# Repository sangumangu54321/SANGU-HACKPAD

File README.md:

SANGU-HACKPAD
Its my personal hackpad made with the help of hack club

# here is the Schematic

# here is the pcb 

# case 

#BOM:
- 6x Cherry MX Switches
- 6x Blank DSA Keycaps
- 3x SK6812 MINI-E LEDs
- 1x XIAO RP2040
- 1x 0.91 inch OLED display
- 4x M3x16 Bolt
- 4x M3 Heatset
- 1x RotaryEncoder_Alps_EC11E_Vertical_H20mm
PLUS 
PCB
FORM JLBPCB

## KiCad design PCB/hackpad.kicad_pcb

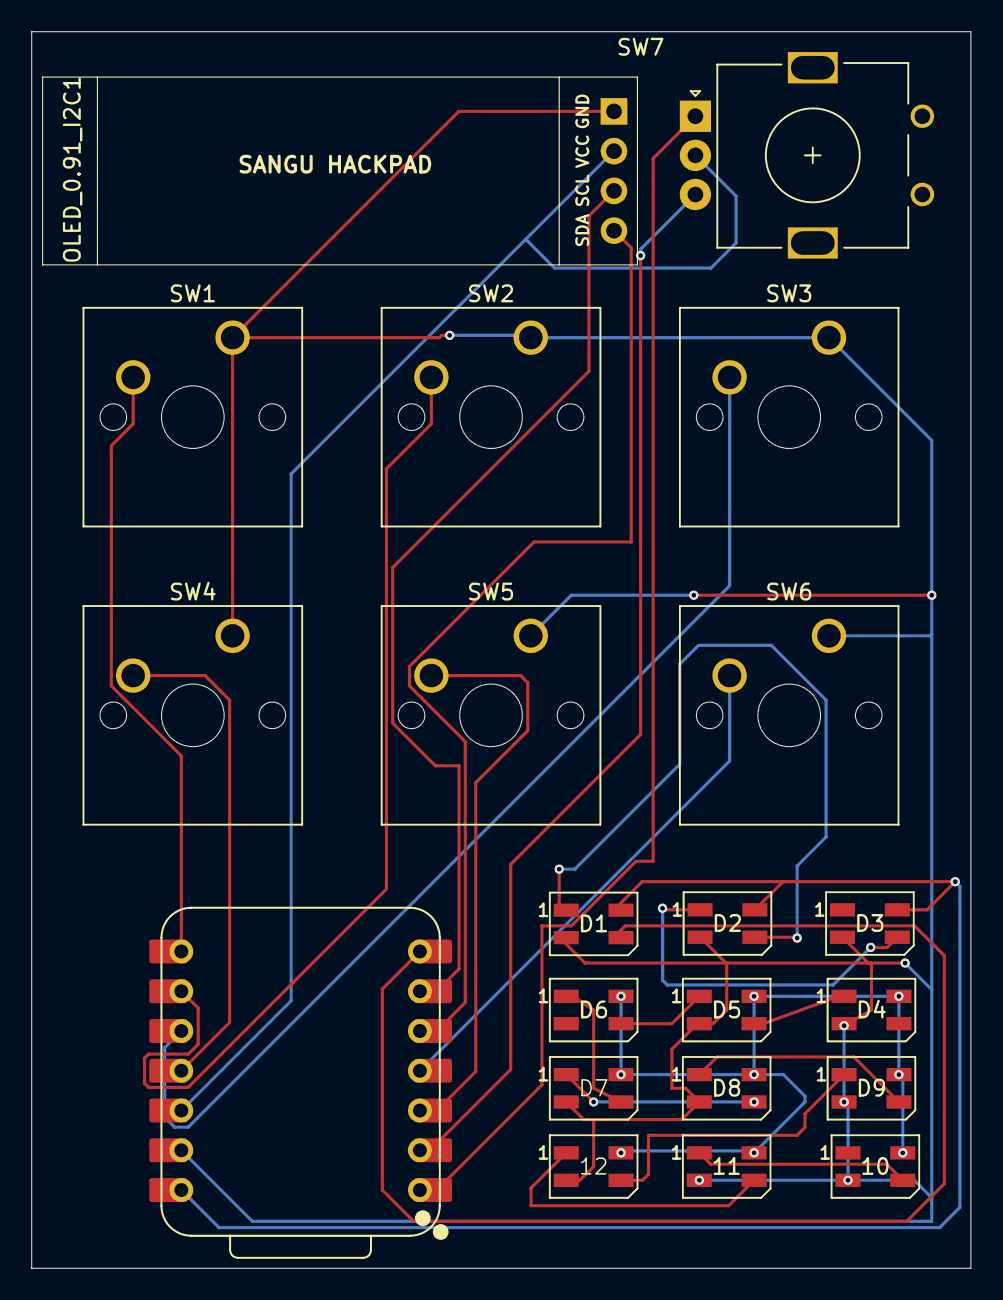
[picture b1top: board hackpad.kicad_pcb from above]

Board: 2 copper layers, 60.0 x 79.0 mm, 21 parts (0 on the bottom side), 25 nets.

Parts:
10, 11, 12: SK6812MINI; LED_SK6812MINI_PLCC4_3.5x3.5mm_P1.75mm
D1, D2, D3, D4, D5, D6, D7, D8, D9: SK6812MINI; LED_SK6812MINI_PLCC4_3.5x3.5mm_P1.75mm
OLED_0.91_I2C1: SSD1306-0.91-OLED-4pin-128x32
SW1, SW2, SW3, SW4, SW5, SW6: SW_Push; SW_Cherry_MX_1.00u_PCB
SW7: RotaryEncoder; RotaryEncoder_Alps_EC11E_Vertical_H20mm
U1: XIAO-RP2040-DIP

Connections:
+3.3V: OLED_0.91_I2C1.2 (VCC), SW7.C, U1.12 (3V3)
+5V: 10.4 (VDD), 11.4 (VDD), 12.4 (VDD), D1.4 (VDD), D2.4 (VDD), D3.4 (VDD), D4.4 (VDD), D5.4 (VDD), D6.4 (VDD), D7.4 (VDD), D8.4 (VDD), D9.4 (VDD), U1.14 (VBUS)
GND: 10.2 (VSS), 11.2 (VSS), 12.2 (VSS), D1.2 (VSS), D2.2 (VSS), D3.2 (VSS), D4.2 (VSS), D5.2 (VSS), D6.2 (VSS), D7.2 (VSS), D8.2 (VSS), D9.2 (VSS), OLED_0.91_I2C1.1 (GND), SW1.1, SW2.1, SW3.1, SW4.1, SW5.1, SW6.1, U1.13 (GND)
unnamed: D1.3 (DIN), U1.7 (GPIO0/TX)
unnamed: D1.1 (DOUT), D2.3 (DIN)
unnamed: D2.1 (DOUT), D3.3 (DIN)
unnamed: D3.1 (DOUT), D4.3 (DIN)
unnamed: D4.1 (DOUT), D5.3 (DIN)
unnamed: D5.1 (DOUT), D6.3 (DIN)
unnamed: D6.1 (DOUT), D7.3 (DIN)
unnamed: D7.1 (DOUT), D8.3 (DIN)
unnamed: D8.1 (DOUT), D9.3 (DIN)
unnamed: 10.3 (DIN), 11.1 (DOUT)
unnamed: 11.3 (DIN), 12.1 (DOUT)
unnamed: 12.3 (DIN), D9.1 (DOUT)
unnamed: OLED_0.91_I2C1.3 (SCL), U1.6 (GPIO7/SCL)
unnamed: OLED_0.91_I2C1.4 (SDA), U1.5 (GPIO6/SDA)
unnamed: SW1.2, U1.8 (GPIO1/RX)
unnamed: SW2.2, U1.9 (GPIO2/SCK)
unnamed: SW4.2, U1.11 (GPIO3/MOSI)
unnamed: SW3.2, U1.10 (GPIO4/MISO)
unnamed: SW7.A, U1.1 (GPIO26/ADC0/A0)
unnamed: SW7.B, U1.2 (GPIO27/ADC1/A1)
unnamed: SW5.2, U1.3 (GPIO28/ADC2/A2)
unnamed: SW6.2, U1.4 (GPIO29/ADC3/A3)

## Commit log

2025-12-30 cad added
